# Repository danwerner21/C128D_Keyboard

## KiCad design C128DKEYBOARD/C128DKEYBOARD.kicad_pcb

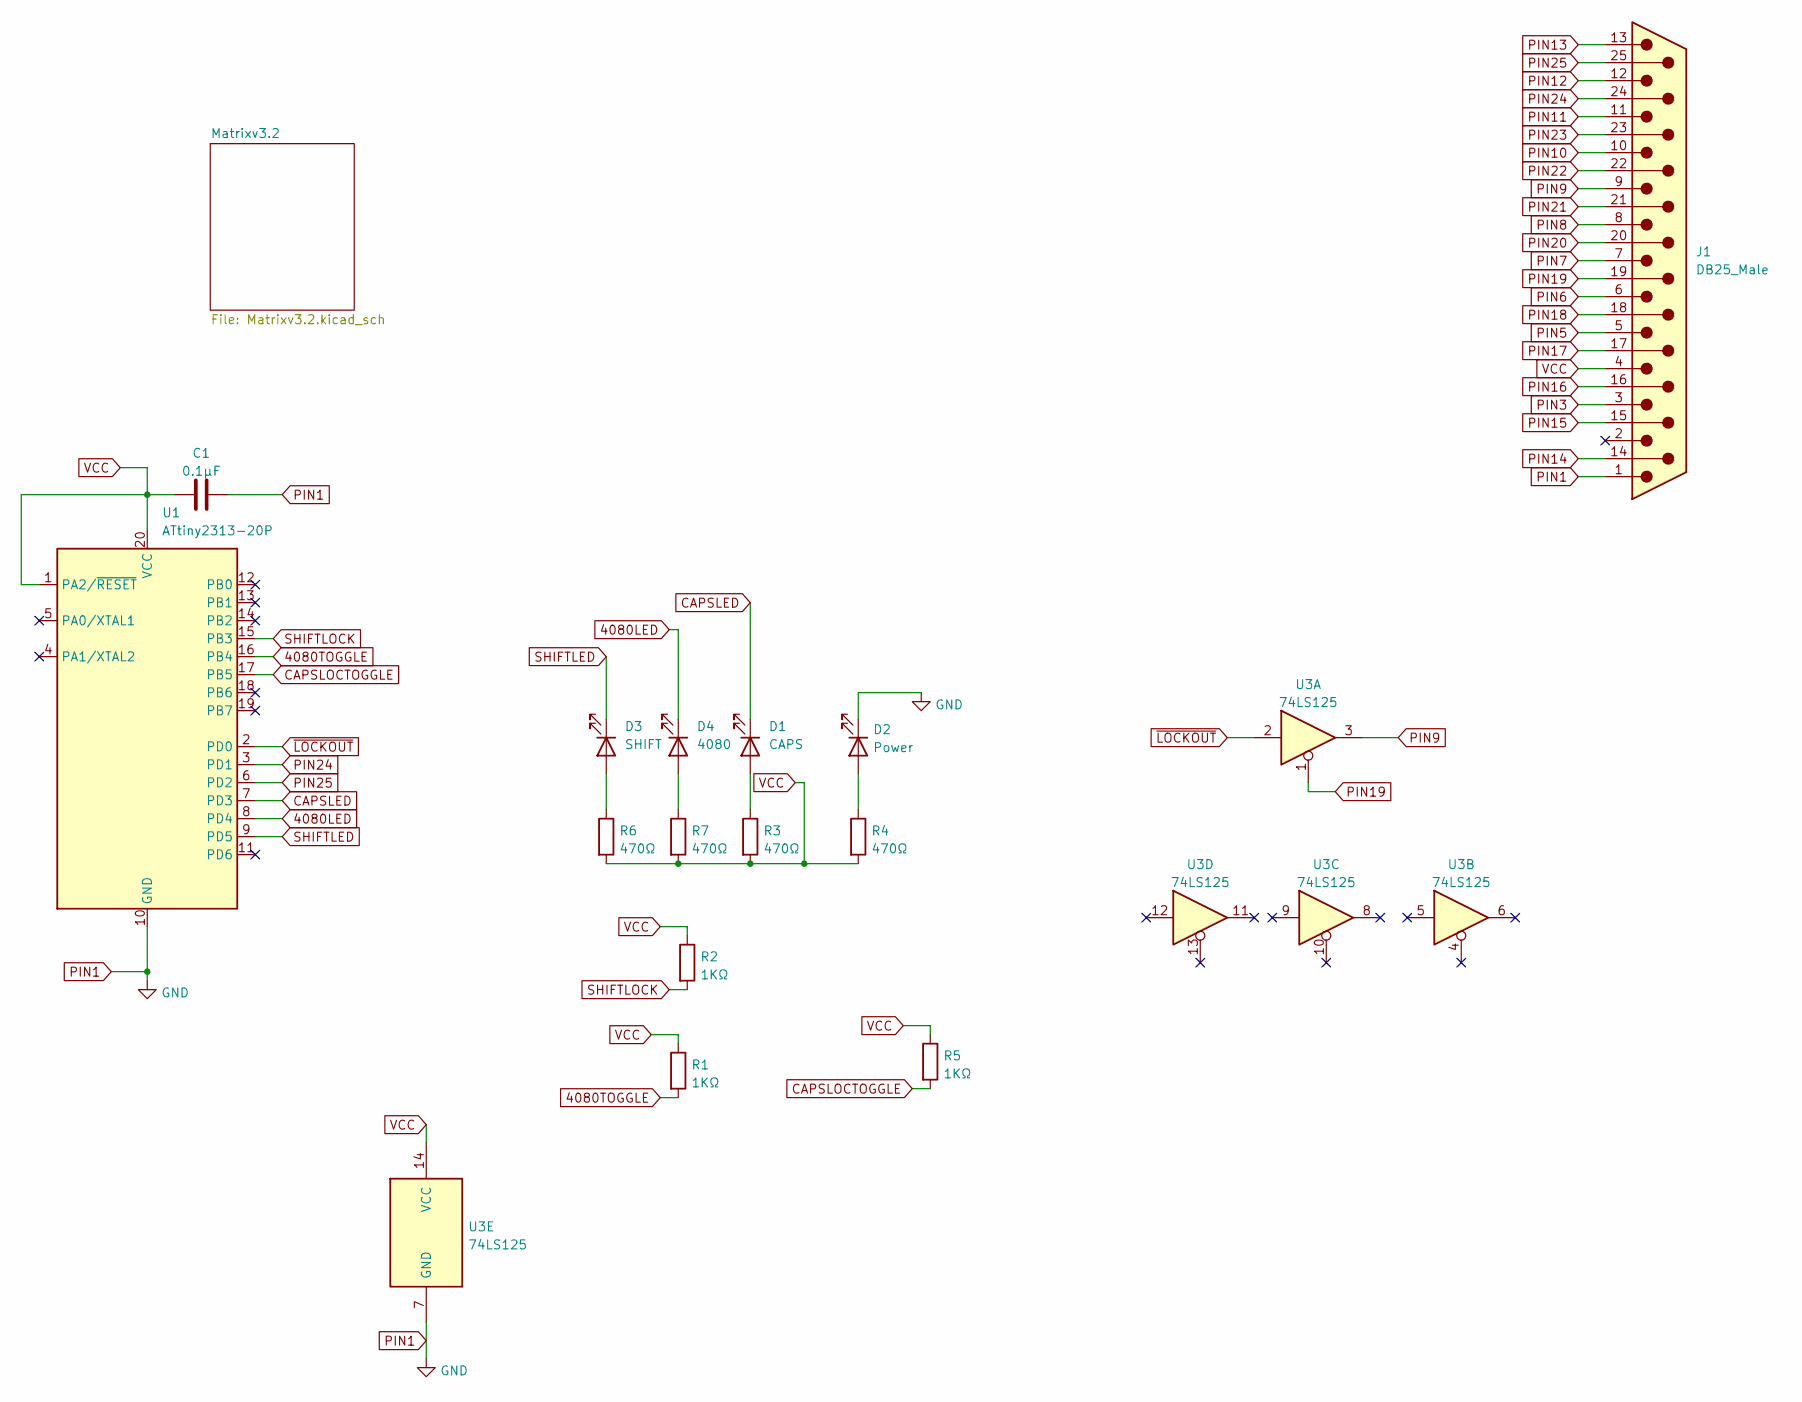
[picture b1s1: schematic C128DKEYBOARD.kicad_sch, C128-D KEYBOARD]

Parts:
C1: 0.1µF; C_Disc_D7.0mm_W2.5mm_P5.00mm
D1: CAPS; LED_D3.0mm
D2: Power; LED_D3.0mm
D3: SHIFT; LED_D3.0mm
D4: 4080; LED_D3.0mm
J1: DB25_Male; DSUB-25_Male_Horizontal_P2.77x2.54mm_EdgePinOffset9.40mm
R1, R2, R5: 1KΩ; R_Axial_DIN0207_L6.3mm_D2.5mm_P7.62mm_Horizontal
R3, R4, R6, R7: 470Ω; R_Axial_DIN0207_L6.3mm_D2.5mm_P7.62mm_Horizontal
U1: ATtiny2313-20P; DIP-20_W7.62mm
U3: 74LS125; DIP-14_W7.62mm_Socket_LongPads

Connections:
4080LED: D4.1 (K), U1.8 (PD4)
4080TOGGLE: R1.2, U1.16 (PB4); also elsewhere on the board
CAPSLED: D1.1 (K), U1.7 (PD3)
CAPSLOCTOGGLE: R5.2, U1.17 (PB5); also elsewhere on the board
unnamed: D1.2 (A), R3.1
unnamed: D2.2 (A), R4.1
unnamed: D3.2 (A), R6.1
unnamed: D4.2 (A), R7.1
PIN1: C1.2, D2.1 (K), J1.1, U1.10 (GND), U3.7 (GND); also elsewhere on the board
PIN3: J1.3; also elsewhere on the board
PIN5: J1.5; also elsewhere on the board
PIN6: J1.6; also elsewhere on the board
PIN7: J1.7; also elsewhere on the board
PIN8: J1.8; also elsewhere on the board
PIN9: J1.9, U3.3; also elsewhere on the board
PIN10: J1.10; also elsewhere on the board
PIN11: J1.11; also elsewhere on the board
PIN12: J1.12; also elsewhere on the board
PIN13: J1.13; also elsewhere on the board
PIN14: J1.14; also elsewhere on the board
PIN15: J1.15; also elsewhere on the board
PIN16: J1.16; also elsewhere on the board
PIN17: J1.17; also elsewhere on the board
PIN18: J1.18; also elsewhere on the board
PIN19: J1.19, U3.1; also elsewhere on the board
PIN20: J1.20; also elsewhere on the board
PIN21: J1.21; also elsewhere on the board
PIN22: J1.22; also elsewhere on the board
PIN23: J1.23; also elsewhere on the board
PIN24: J1.24, U1.3 (PD1)
PIN25: J1.25, U1.6 (PD2)
SHIFTLED: D3.1 (K), U1.9 (PD5)
SHIFTLOCK: R2.2, U1.15 (PB3); also elsewhere on the board
VCC: C1.1, J1.4, R1.1, R2.1, R3.2, R4.2, R5.1, R6.2, R7.2, U1.1 (PA2/~RESET), U1.20 (VCC), U3.14 (VCC)
~LOCKOUT: U1.2 (PD0), U3.2

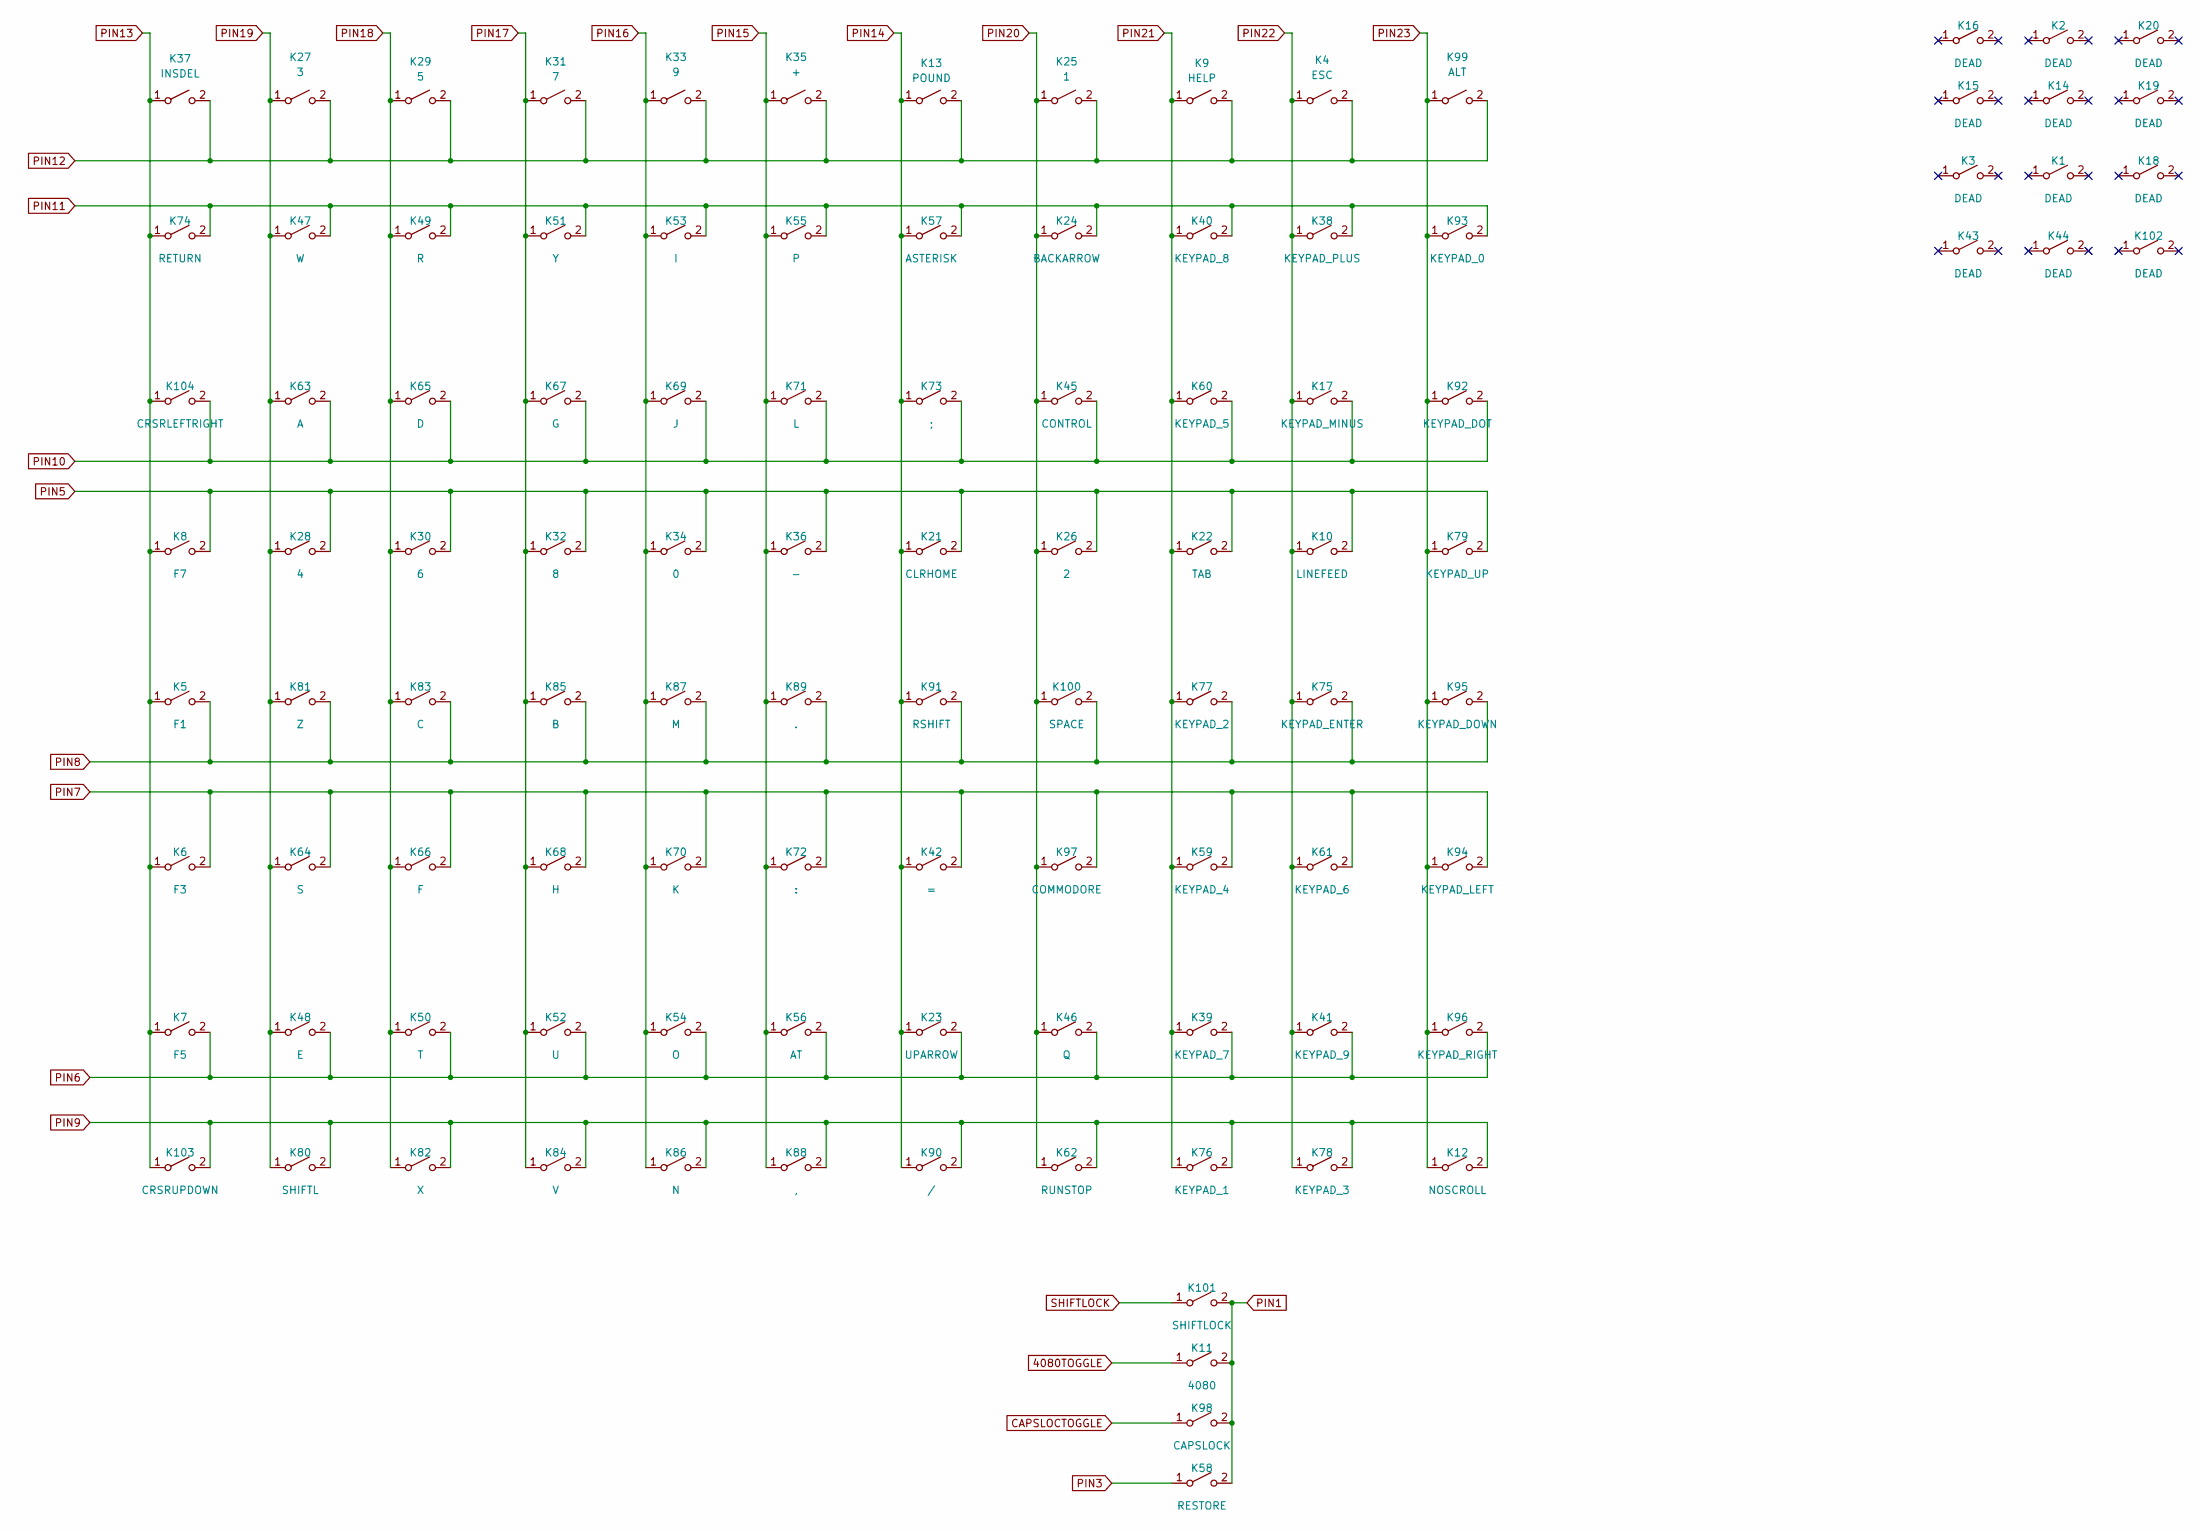
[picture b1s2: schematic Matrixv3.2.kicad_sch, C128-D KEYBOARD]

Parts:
K1, K2, K3, K14, K15, K16, K18, K19, K20, K43, K44: DEAD; CHERRY_PLATE_100H
K4: ESC; CHERRY_PLATE_100H
K5: F1; CHERRY_PLATE_100H
K6: F3; CHERRY_PLATE_100H
K7: F5; CHERRY_PLATE_100H
K8: F7; CHERRY_PLATE_100H
K9: HELP; CHERRY_PLATE_100H
K10: LINEFEED; CHERRY_PLATE_100H
K11: 4080; CHERRY_PLATE_100H
K12: NOSCROLL; CHERRY_PLATE_100H
K13: POUND; CHERRY_PLATE_100H
K17: KEYPAD_MINUS; CHERRY_PLATE_100H
K21: CLRHOME; CHERRY_PLATE_100H
K22: TAB; CHERRY_PLATE_100H
K23: UPARROW; CHERRY_PLATE_100H
K24: BACKARROW; CHERRY_PLATE_100H
K25: 1; CHERRY_PLATE_100H
K26: 2; CHERRY_PLATE_100H
K27: 3; CHERRY_PLATE_100H
K28: 4; CHERRY_PLATE_100H
K29: 5; CHERRY_PLATE_100H
K30: 6; CHERRY_PLATE_100H
K31: 7; CHERRY_PLATE_100H
K32: 8; CHERRY_PLATE_100H
K33: 9; CHERRY_PLATE_100H
K34: 0; CHERRY_PLATE_100H
K35: +; CHERRY_PLATE_100H
K36: -; CHERRY_PLATE_100H
K37: INSDEL; CHERRY_PLATE_200H
K38: KEYPAD_PLUS; CHERRY_PLATE_200V
K39: KEYPAD_7; CHERRY_PLATE_100H
K40: KEYPAD_8; CHERRY_PLATE_100H
K41: KEYPAD_9; CHERRY_PLATE_100H
K42: =; CHERRY_PLATE_100H
K45: CONTROL; CHERRY_PLATE_150H
K46: Q; CHERRY_PLATE_100H
K47: W; CHERRY_PLATE_100H
K48: E; CHERRY_PLATE_100H
K49: R; CHERRY_PLATE_100H
K50: T; CHERRY_PLATE_100H
K51: Y; CHERRY_PLATE_100H
K52: U; CHERRY_PLATE_100H
K53: I; CHERRY_PLATE_100H
K54: O; CHERRY_PLATE_100H
K55: P; CHERRY_PLATE_100H
K56: AT; CHERRY_PLATE_100H
K57: ASTERISK; CHERRY_PLATE_100H
K58: RESTORE; CHERRY_PLATE_150H
K59: KEYPAD_4; CHERRY_PLATE_100H
K60: KEYPAD_5; CHERRY_PLATE_100H
K61: KEYPAD_6; CHERRY_PLATE_100H
K62: RUNSTOP; CHERRY_PLATE_175H
K63: A; CHERRY_PLATE_100H
K64: S; CHERRY_PLATE_100H
K65: D; CHERRY_PLATE_100H
K66: F; CHERRY_PLATE_100H
K67: G; CHERRY_PLATE_100H
K68: H; CHERRY_PLATE_100H
K69: J; CHERRY_PLATE_100H
K70: K; CHERRY_PLATE_100H
K71: L; CHERRY_PLATE_100H
K72: :; CHERRY_PLATE_100H
K73: ;; CHERRY_PLATE_100H
K74: RETURN; CHERRY_PLATE_225H
K75: KEYPAD_ENTER; CHERRY_PLATE_200V
K76: KEYPAD_1; CHERRY_PLATE_100H
K77: KEYPAD_2; CHERRY_PLATE_100H
K78: KEYPAD_3; CHERRY_PLATE_100H
K79: KEYPAD_UP; CHERRY_PLATE_100H
K80: SHIFTL; CHERRY_PLATE_225H
K81: Z; CHERRY_PLATE_100H
K82: X; CHERRY_PLATE_100H
K83: C; CHERRY_PLATE_100H
K84: V; CHERRY_PLATE_100H
K85: B; CHERRY_PLATE_100H
K86: N; CHERRY_PLATE_100H
K87: M; CHERRY_PLATE_100H
K88: ,; CHERRY_PLATE_100H
K89: .; CHERRY_PLATE_100H
K90: /; CHERRY_PLATE_100H
K91: RSHIFT; CHERRY_PLATE_275H
K92: KEYPAD_DOT; CHERRY_PLATE_100H
K93: KEYPAD_0; CHERRY_PLATE_200H
K94: KEYPAD_LEFT; CHERRY_PLATE_100H
K95: KEYPAD_DOWN; CHERRY_PLATE_100H
K96: KEYPAD_RIGHT; CHERRY_PLATE_100H
K97: COMMODORE; CHERRY_PLATE_125H
K98: CAPSLOCK; CHERRY_PLATE_125H
K99: ALT; CHERRY_PLATE_125H
K100: SPACE; CHERRY_PLATE_625H
K101: SHIFTLOCK; CHERRY_PLATE_125H
K102: DEAD; CHERRY_PLATE_125H
K103: CRSRUPDOWN; CHERRY_PLATE_125H
K104: CRSRLEFTRIGHT; CHERRY_PLATE_125H

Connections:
4080TOGGLE: K11.1 (A); also elsewhere on the board
CAPSLOCTOGGLE: K98.1 (A); also elsewhere on the board
PIN1: K11.2 (B), K58.2 (B), K98.2 (B), K101.2 (B); also elsewhere on the board
PIN3: K58.1 (A); also elsewhere on the board
PIN5: K8.2 (B), K10.2 (B), K21.2 (B), K22.2 (B), K26.2 (B), K28.2 (B), K30.2 (B), K32.2 (B), K34.2 (B), K36.2 (B), K79.2 (B); also elsewhere on the board
PIN6: K7.2 (B), K23.2 (B), K39.2 (B), K41.2 (B), K46.2 (B), K48.2 (B), K50.2 (B), K52.2 (B), K54.2 (B), K56.2 (B), K96.2 (B); also elsewhere on the board
PIN7: K6.2 (B), K42.2 (B), K59.2 (B), K61.2 (B), K64.2 (B), K66.2 (B), K68.2 (B), K70.2 (B), K72.2 (B), K94.2 (B), K97.2 (B); also elsewhere on the board
PIN8: K5.2 (B), K75.2 (B), K77.2 (B), K81.2 (B), K83.2 (B), K85.2 (B), K87.2 (B), K89.2 (B), K91.2 (B), K95.2 (B), K100.2 (B); also elsewhere on the board
PIN9: K12.2 (B), K62.2 (B), K76.2 (B), K78.2 (B), K80.2 (B), K82.2 (B), K84.2 (B), K86.2 (B), K88.2 (B), K90.2 (B), K103.2 (B); also elsewhere on the board
PIN10: K17.2 (B), K45.2 (B), K60.2 (B), K63.2 (B), K65.2 (B), K67.2 (B), K69.2 (B), K71.2 (B), K73.2 (B), K92.2 (B), K104.2 (B); also elsewhere on the board
PIN11: K24.2 (B), K38.2 (B), K40.2 (B), K47.2 (B), K49.2 (B), K51.2 (B), K53.2 (B), K55.2 (B), K57.2 (B), K74.2 (B), K93.2 (B); also elsewhere on the board
PIN12: K4.2 (B), K9.2 (B), K13.2 (B), K25.2 (B), K27.2 (B), K29.2 (B), K31.2 (B), K33.2 (B), K35.2 (B), K37.2 (B), K99.2 (B); also elsewhere on the board
PIN13: K5.1 (A), K6.1 (A), K7.1 (A), K8.1 (A), K37.1 (A), K74.1 (A), K103.1 (A), K104.1 (A); also elsewhere on the board
PIN14: K13.1 (A), K21.1 (A), K23.1 (A), K42.1 (A), K57.1 (A), K73.1 (A), K90.1 (A), K91.1 (A); also elsewhere on the board
PIN15: K35.1 (A), K36.1 (A), K55.1 (A), K56.1 (A), K71.1 (A), K72.1 (A), K88.1 (A), K89.1 (A); also elsewhere on the board
PIN16: K33.1 (A), K34.1 (A), K53.1 (A), K54.1 (A), K69.1 (A), K70.1 (A), K86.1 (A), K87.1 (A); also elsewhere on the board
PIN17: K31.1 (A), K32.1 (A), K51.1 (A), K52.1 (A), K67.1 (A), K68.1 (A), K84.1 (A), K85.1 (A); also elsewhere on the board
PIN18: K29.1 (A), K30.1 (A), K49.1 (A), K50.1 (A), K65.1 (A), K66.1 (A), K82.1 (A), K83.1 (A); also elsewhere on the board
PIN19: K27.1 (A), K28.1 (A), K47.1 (A), K48.1 (A), K63.1 (A), K64.1 (A), K80.1 (A), K81.1 (A); also elsewhere on the board
PIN20: K24.1 (A), K25.1 (A), K26.1 (A), K45.1 (A), K46.1 (A), K62.1 (A), K97.1 (A), K100.1 (A); also elsewhere on the board
PIN21: K9.1 (A), K22.1 (A), K39.1 (A), K40.1 (A), K59.1 (A), K60.1 (A), K76.1 (A), K77.1 (A); also elsewhere on the board
PIN22: K4.1 (A), K10.1 (A), K17.1 (A), K38.1 (A), K41.1 (A), K61.1 (A), K75.1 (A), K78.1 (A); also elsewhere on the board
PIN23: K12.1 (A), K79.1 (A), K92.1 (A), K93.1 (A), K94.1 (A), K95.1 (A), K96.1 (A), K99.1 (A); also elsewhere on the board
SHIFTLOCK: K101.1 (A); also elsewhere on the board

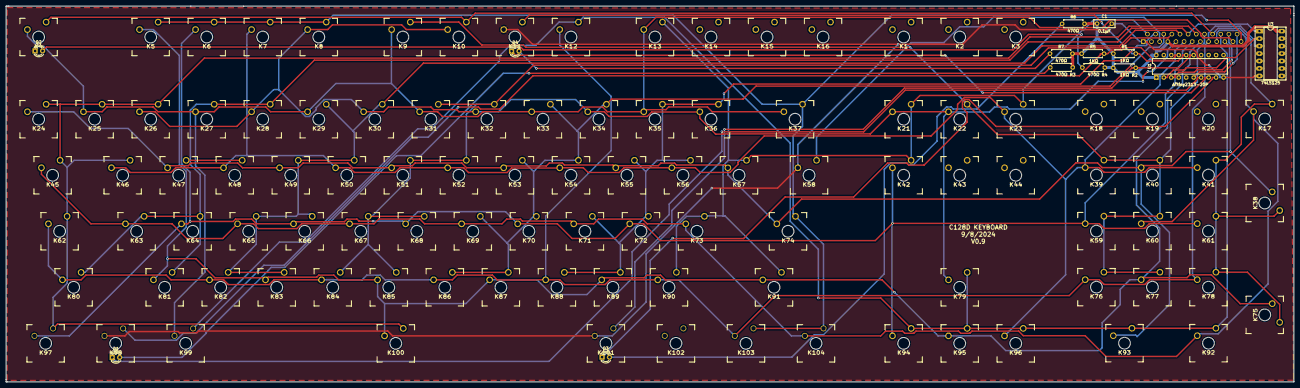
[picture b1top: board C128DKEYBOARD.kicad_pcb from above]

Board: 2 copper layers, 437.8 x 127.8 mm, 119 parts (1 on the bottom side), 35 nets.

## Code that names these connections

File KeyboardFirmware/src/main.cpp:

#include <Arduino.h>

//========================================================================
// Hardwiring the ATtiny2313
//========================================================================
/*
                             ____  ____
               /RESET (PA2) -|1  \/   |- (Vcc)
                 LOCK (PD0) -|2     19|- (PB7) nc
                PIN24 (PD1) -|3     18|- (PB6) nc
                   nc (PA0) -|4     17|- (PB5) CAPSLOCTOGGLE
                   nc (PA2) -|5     16|- (PB4) S4080TOGGLE
                PIN25 (PD2) -|6     15|- (PB3) SHIFTLOCK
              CAPSLED (PD3) -|7     14|- (PB2) nc
             S4080LED (PD4) -|8     13|- (PB1) nc
             SHIFTLED (PD5) -|9     12|- (PB0) nc
                      (GND) -|________|- (PD6) nc

*/

#define CAPSLOCKPIN 14
#define S4080PIN 13
#define SHIFTLOCKPIN 12

#define CAPSLOCKLED 5
#define S4080LED 6
#define SHIFTLOCKLED 7

#define LOCKOUT 0
#define PIN24 1
#define PIN25 4


static int capslock = 0;
static int s4080 = 0;
static int shiftlock = 0;

static int shiftState = LOW; //this variable tracks the state of the button, low if not pressed, high if pressed
static unsigned long shiftlastDebounceTime = 0;  // the last time the output pin was toggled

static int capsState = LOW; //this variable tracks the state of the button, low if not pressed, high if pressed
static unsigned long capslastDebounceTime = 0;  // the last time the output pin was toggled

static int s4080State = LOW; //this variable tracks the state of the button, low if not pressed, high if pressed
static unsigned long  s4080lastDebounceTime = 0;  // the last time the output pin was toggled

static unsigned long  debounceDelay = 50;    // the debounce time; increase if the output flickers


void setup()
{
  pinMode(CAPSLOCKLED, OUTPUT);
  digitalWrite(CAPSLOCKLED, HIGH);
  pinMode(S4080LED, OUTPUT);
  digitalWrite(S4080LED, HIGH);
  pinMode(SHIFTLOCKLED, OUTPUT);
  digitalWrite(SHIFTLOCKLED, HIGH);

  pinMode(CAPSLOCKPIN, INPUT);
  pinMode(S4080PIN, INPUT);
  pinMode(SHIFTLOCKPIN, INPUT);

  pinMode(LOCKOUT, OUTPUT);
  pinMode(PIN24, OUTPUT);
  pinMode(PIN25, OUTPUT);
  digitalWrite(LOCKOUT, HIGH);
  digitalWrite(PIN24, HIGH);
  digitalWrite(PIN25, HIGH);
}

void loop() {
  capsState = digitalRead(CAPSLOCKPIN);
  shiftState = digitalRead(SHIFTLOCKPIN);
  s4080State = digitalRead(S4080PIN);

// CAPS LOCK PROCESSING
  if ( (millis() - capslastDebounceTime) > debounceDelay) {
    if ( (capsState == LOW) && (capslock == 0) ) {
      digitalWrite(CAPSLOCKLED, LOW); //turn LED on
      digitalWrite(PIN25, LOW);
      capslock=1;
      capslastDebounceTime = millis(); //set the current time
    }
    else if ( (capsState == LOW) && (capslock != 0) ) {
      digitalWrite(CAPSLOCKLED, HIGH); //turn LED off
      digitalWrite(PIN25, HIGH);
      capslock=0;
      capslastDebounceTime = millis(); //set the current time
    }
  }

// S4080 LOCK PROCESSING
  if ( (millis() - s4080lastDebounceTime) > debounceDelay) {
    if ( (s4080State == LOW) && (s4080 == 0) ) {
      digitalWrite(S4080LED, LOW); //turn LED on
      digitalWrite(PIN24, LOW);
      s4080=1;
      s4080lastDebounceTime = millis(); //set the current time
    }
    else if ( (s4080State == LOW) && (s4080 != 0) ) {
      digitalWrite(S4080LED, HIGH); //turn LED off
      digitalWrite(PIN24, HIGH);
      s4080=0;
      s4080lastDebounceTime = millis(); //set the current time
    }
  }

// SHIFT LOCK PROCESSING
  if ( (millis() - shiftlastDebounceTime) > debounceDelay) {
    if ( (shiftState == LOW) && (shiftlock == 0) ) {
      digitalWrite(SHIFTLOCKLED, LOW); //turn LED on
      digitalWrite(LOCKOUT, LOW);
      shiftlock=1;
      shiftlastDebounceTime = millis(); //set the current time
    }
    else if ( (shiftState == LOW) && (shiftlock != 0) ) {
      digitalWrite(SHIFTLOCKLED, HIGH); //turn LED off
      digitalWrite(LOCKOUT, HIGH);
      shiftlock=0;
      shiftlastDebounceTime = millis(); //set the current time
    }
  }



}

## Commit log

2024-09-22 initial
2024-09-27 update layout
